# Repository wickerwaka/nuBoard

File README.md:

# nuBoard

The repository includes board hardware, RP2040 firmware, an Efinix runtime
template, and Linux host tools. See [`mcu/README.md`](mcu/README.md),
[`fpga/template/README.md`](fpga/template/README.md),
[`host/README.md`](host/README.md), and [`docs/protocol.md`](docs/protocol.md).

The [68000 differential harness](docs/m68000-harness.md) runs reset-executable
tests against fx68k in Verilator or the FPGA, and supports an explicitly armed
MC68000 daughterboard lane. MCU firmware stays CPU-independent.

KiCad 10 hardware projects copied from the working `nu68020/nuBoard` directory.

| Project | Open this file |
| --- | --- |
| Main board | `hardware/main-board/nuBoard.kicad_pro` |
| Daughter board template | `hardware/daughter-template/nuDaughter.kicad_pro` |
| 68000 daughter board | `hardware/68000/68000.kicad_pro` |
| Motorola 68020 daughter board | `hardware/68020/68020.kicad_pro` |
| Motorola 68020 four-layer alternative | `hardware/68020-4layer/68020-4layer.kicad_pro` |
| Motorola 68030 daughter board | `hardware/68030/68030.kicad_pro` |
| Motorola 68030 four-layer alternative | `hardware/68030-4layer/68030-4layer.kicad_pro` |
| NEC V35S daughter board | `hardware/v35s/v35s.kicad_pro` |

Each daughter project has its own `nuBoard.kicad_sym`, `nuBoard.pretty`, and
project-relative library tables. Either directory can be copied independently;
the only libraries required outside it are the default KiCad 10 libraries.
Keep these local libraries with the project when copying or distributing it.
The main board also uses project-relative custom libraries and bundled models.

To create a daughter board, copy the entire `hardware/daughter-template` directory,
or select it with KiCad's New Project from Template dialog. Its `meta` directory
contains template metadata. Keep the library filenames as `nuBoard.*`; KiCad
renames files containing `nuDaughter` when creating a project from the template.
Filename-specific sheet metadata and annotation history have been removed from
the template settings so new projects can be renamed and annotated cleanly.

Existing production exports, notes, design blocks, models, and supporting data
are preserved beside their projects. Production exports are historical snapshots;
regenerate them before fabrication. Backups and personal editor state were copied
locally but are excluded from Git. The original source directory is untouched.

## Konnect MCP

Open your MCP client from the repository root. `.mcp.json` configures Konnect for
compatible clients; `.codex/config.toml` configures it for Codex, following the
[official MCP configuration documentation](https://developers.openai.com/codex/mcp/).
Codex loads project configuration for trusted projects. Restart the client after
opening this repository to load the server.

Both configurations run `sh scripts/konnect.sh`, which uses `bin/konnect` when
present, otherwise `konnect` on PATH. This checkout includes a local copy of the
existing Konnect v0.2.0 macOS arm64 executable in `bin/konnect`; the binary is
ignored by Git. On another machine, install a compatible Konnect executable on
PATH or place it in `bin/konnect` and make it executable.

Check the installation with `sh scripts/konnect.sh --version` and
`sh scripts/konnect.sh status`. For live PCB operations, open the intended PCB in
KiCad and enable its IPC API. Explicitly select the intended project when using
Konnect because this repository contains three boards.

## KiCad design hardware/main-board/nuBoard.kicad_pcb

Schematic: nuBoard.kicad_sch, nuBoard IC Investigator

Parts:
C1, C131: 4.7u; C_0402_1005Metric; JLCPCB Part C23733
C2, C3, C101, C104, C107, C110, C113, C116, C117, C132, C145, C146, C147, C148, C149, C150, C151, C152, C153, C154, C155, C156, C157, C158, C159, C160, C161, C162, C163, C164, C165, C166, C167, C168, C169, C170, C171, C172, C173, C174, C175, C176, C177, C178, C179, C180, C181, C182, C183, C184, C185, C186, C187, C188, C189, C190, C191, C192, C193, C194: 0.1u; C_0402_1005Metric; JLCPCB Part C1525
C4, C133, C134: 0.01u; C_0402_1005Metric; JLCPCB Part C15195
C5, C6, C7, C8, C9, C10, C11, C12, C13, C14, C15, C16, C17, C18, C19, C20, C21, C22, C23, C24, C25, C26, C27, C28, C29, C30, C31, C32, C33, C34, C35, C36, C37, C38, C39, C118, C119, C120, C121, C122, C123, C124, C125, C128, C129, C130: 0.1u 0201; C_0201_0603Metric; JLCPCB Part C5142565
C40, C41, C42, C43, C44, C45, C46, C47, C48, C49, C50, C51, C52, C53, C54, C55, C56, C57, C58, C59, C60, C61, C62, C63, C64, C65, C66, C67, C68, C69, C70, C71, C72, C73, C74, C75, C76, C77, C78, C79, C80, C81, C82, C83: 0.01u 0201; C_0201_0603Metric; JLCPCB Part C285010
C84, C85, C88, C89: 1u; C_0805_2012Metric; JLCPCB Part C28323
C86, C87, C90, C91, C93, C97, C100, C114, C115: 10u; C_0805_2012Metric; JLCPCB Part C15850
C92, C94, C95, C96, C98, C99, C126, C127: 1u; C_0402_1005Metric; JLCPCB Part C52923
C102, C103, C108, C109: 22u; C_0402_1005Metric; JLCPCB Part C22367823
C105, C106, C111, C112: 10u; C_0402_1005Metric; JLCPCB Part C315248
D1, D2, D3, D4: LED; LED_0603_1608Metric; JLCPCB Part C2286
FB1: 33ohm 100mhz; L_0402_1005Metric; JLCPCB Part C160974
H1, H2, H3, H4, H5, H6: MountingHole_Pad; MountingHole_3.2mm_M3_ISO7380
H7, H8, H9, H10, H11, H12, H13: MountingHole_Pad; MountingHole_3.2mm_M3
J1: FPGA Debug; PinHeader_2x05_P1.27mm_Vertical_SMD; JLCPCB Part C41376037
J2: Barrel_Jack_Switch; BarrelJack_Wuerth_6941xx301002
J3: USB_C_Receptacle_USB2.0_16P; USB_C_Receptacle_HCTL_HC-TYPE-C-16P-01A; JLCPCB Part C2894897
J4: MCU Debug; PinHeader_2x05_P1.27mm_Vertical_SMD; JLCPCB Part C41376037
J5, J6, J7, J8: Conn_01x34_Socket; PinSocket_1x34_P2.54mm_Vertical
L1, L2: 2.2uH; L_1008_2520Metric; JLCPCB Part C964122
Q1: NVF5P03T3G; SOT-223-3_TabPin2; JLCPCB Part C895162
Q2: BSR802NL6327; SOT-23; JLCPCB Part C5240463
R1, R2, R3, R4, R5, R6, R7, R8, R9, R10, R11, R13, R14, R15, R17, R18, R24, R27, R28, R31, R32, R33, R39, R40, R56, R57, R58, R59, R60, R61, R62, R63, R64, R65, R66, R67, R68, R70, R72, R74, R76, R77, R78, R79: 10K; R_0402_1005Metric; JLCPCB Part C25744
R12, R29, R30, R69, R71, R73, R75: 22; R_0402_1005Metric; JLCPCB Part C25092
R16, R19, R35, R38, R42, R43: 1K; R_0402_1005Metric; JLCPCB Part C11702
R20, R21: 5.1K; R_0402_1005Metric; JLCPCB Part C25905
R22: 33.2K 1%; R_0402_1005Metric; JLCPCB Part C122548
R23, R26: 10K 1%; R_0402_1005Metric; JLCPCB Part C25744
R25: 5.76K 1%; R_0402_1005Metric; JLCPCB Part C11590
R34: 400; R_0402_1005Metric; JLCPCB Part C2909358
R36, R37, R41: 27; R_0402_1005Metric; JLCPCB Part C25100
RN1, RN2, RN3, RN4, RN5, RN6, RN7, RN8, RN9, RN10, RN11, RN12, RN13, RN14, RN15, RN16, RN17, RN18, RN19, RN20, RN21, RN22, RN23, RN24: 22R; YC248-JR-0722RL; Manufacturer Part YC248-JR-0722RL; LCSC C695207
SW1: MCU_Reset; SW_SPST_Omron_B3FS-100xP; JLCPCB Part C271750
SW2: MCU_Boot; SW_SPST_Omron_B3FS-100xP; JLCPCB Part C271750
TP1: +5V; TestPoint_Pad_D1.0mm
TP2: +3.3V; TestPoint_Pad_D1.0mm
TP3: +1.2V; TestPoint_Pad_D1.0mm
TP4: VCC_DUT; TestPoint_Pad_D1.0mm
TP5: VCCB; TestPoint_Pad_D1.0mm
U1: T120F484; LFBGA-484_18x18mm_Layout22x22_P0.8mm; JLCPCB Part C3277977
U2: IS66WVH8M8BLL-100B1LI; ISSI_TFBGA-24_6x8mm_P1.0mm; JLCPCB Part C1349096
U3: TPS2116DRL; SOT-583-8; JLCPCB Part C3235557
U4, U5: AP2112K-3.3; SOT-23-5; JLCPCB Part C23380830
U6, U7: TPS563201; SOT-23-6; JLCPCB Part C116592
U8: UCC27524D; SOIC-8_3.9x4.9mm_P1.27mm; JLCPCB Part C465729
U9: TPS2111APWR; SOP65P640X120-8N; JLCPCB Part C471060
U10: W25Q128JVS; SOIC-8_5.3x5.3mm_P1.27mm; JLCPCB Part C97521
U11: RP2040; QFN-56-1EP_7x7mm_P0.4mm_EP3.2x3.2mm; JLCPCB Part C2040
U24, U25, U26, U27, U28, U29, U30, U31, U32, U33, U34, U35: SN74LVC8T245PWR; TSSOP-24_4.4x7.8mm_P0.65mm; JLCPCB Part C27643
U36, U41: TXS0108EPW; TSSOP-20_4.4x6.5mm_P0.65mm; JLCPCB Part C17206
U37, U38, U39, U40: SN74LVC1T45DRL; SOT-563; JLCPCB Part C352970
Y1: 50Mhz; Oscillator_SMD_Abracon_ASE-4Pin_3.2x2.5mm; JLCPCB Part C717684
Y2: 12Mhz; Oscillator_SMD_Abracon_ASE-4Pin_3.2x2.5mm; JLCPCB Part C596950

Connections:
+1.1V_MCU: C127.1, C128.1, C129.1, U11.23 (DVDD), U11.45 (VREG_VOUT), U11.50 (DVDD)
+1.2V: C5.1, C6.1, C7.1, C8.1, C9.1, C10.1, C11.1, C12.1, C13.1, C14.1, C15.1, C16.1, C17.1, C18.1, C19.1, C20.1, C21.1, C40.1, C41.1, C42.1, C43.1, C44.1, C45.1, C46.1, C47.1, C48.1, C49.1, C50.1, C51.1, C52.1, C53.1, C54.1, C55.1, C56.1, C57.1, C58.1, C59.1, C60.1, C61.1, C62.1, C63.1, C64.1, C65.1, C66.1, C67.1, C84.1, C85.1, C86.1, C87.1, C108.1, C109.1, L2.2, R25.1, TP3.1 (1_1), U1.D5 (VCCA_TL), U1.D17 (VCCA_TR), U1.E17 (VCCA_TR), U1.H10 (VCC), U1.J9 (VCC), U1.J11 (VCC), U1.J13 (VCC), U1.J15 (VCC), U1.K10 (VCC), U1.K12 (VCC), U1.K14 (VCC), U1.L9 (VCC), U1.L11 (VCC), U1.L13 (VCC), U1.M8 (VCC), U1.M10 (VCC), U1.M12 (VCC), U1.M14 (VCC), U1.N9 (VCC), U1.N11 (VCC), U1.N13 (VCC), U1.N15 (VCCA_BR), U1.P10 (VCC), U1.P12 (VCC), U1.P14 (VCC), U1.P15 (VCCA_BR), U1.R11 (VCC), U1.W5 (VCCA_BL)
+3.3V: C3.1, C4.1, C22.1, C23.1, C24.1, C25.1, C26.1, C27.1, C28.1, C29.1, C30.1, C31.1, C32.1, C33.1, C34.1, C35.1, C36.1, C37.1, C38.1, C39.1, C68.1, C69.1, C70.1, C71.1, C72.1, C73.1, C74.1, C75.1, C76.1, C77.1, C78.1, C79.1, C80.1, C81.1, C82.1, C83.1, C88.1, C89.1, C90.1, C91.1, C102.1, C103.1, C133.1, C134.1, C145.1, C148.1, C151.1, C154.1, C157.1, C160.1, C163.1, C166.1, C169.1, C172.1, C175.1, C178.1, C181.1, C183.1, C185.1, C187.1, C189.1, C191.1, C192.1, C193.1, FB1.2, J1.1, L1.2, R1.1, R2.1, R3.1, R4.1, R5.1, R6.1, R7.1, R8.1, R9.1, R10.1, R11.1, R13.1, R14.1, R15.1, R22.1, R28.1, R56.1, R57.1, R58.1, R59.1, R60.1, R61.1, R62.1, R63.1, R64.1, R65.1, R66.1, R67.1, R68.1, R77.1, R78.1, R79.1, TP2.1 (1_1), U1.AA4 (VCCIO4F), U1.AA14 (VCCIO4B), U1.B3 (VCCIO2A), U1.B18 (VCCIO3D_TR_BR), U1.C8 (VCCIO2B), U1.C9 (VCCIO2C), U1.C14 (VCCIO2E), U1.C17 (VCCIO2F), U1.C20 (VCCIO3D_TR_BR), U1.D3 (VCCIO2A), U1.D6 (VCCIO2B), U1.D12 (VCCIO2D), U1.F2 (VCCIO1F_1G), U1.F3 (VCCIO1F_1G), U1.F9 (VCCIO2C), U1.F11 (VCCIO2D), U1.F14 (VCCIO2E), U1.G16 (VCCIO2F), U1.J6 (VCCIO1D_1E), U1.K3 (VCCIO1D_1E), U1.N3 (VCCIO1B_1C), U1.N6 (VCCIO1B_1C), U1.R5 (VCCIO1B_1C), U1.R9 (VCCIO4E), U1.T9 (VCCIO4D), U1.T11 (VCCIO4C), U1.U3 (VCCIO1A), U1.U15 (VCCIO4A), U1.V13 (VCCIO4B), U1.W7 (VCCIO4E), U1.Y3 (VCCIO4F), U1.Y9 (VCCIO4D), U1.Y12 (VCCIO4C), U1.Y16 (VCCIO4A), U2.B4 (VCC), U2.D1 (VCCQ), U2.E4 (VCCQ), U24.1 (VCCA), U25.1 (VCCA), U26.1 (VCCA), U27.1 (VCCA), U28.1 (VCCA), U29.1 (VCCA), U30.1 (VCCA), U31.1 (VCCA), U32.1 (VCCA), U33.1 (VCCA), U34.1 (VCCA), U35.1 (VCCA), U36.2 (VCCA), U37.1 (VCCA), U38.1 (VCCA), U39.1 (VCCA), U40.1 (VCCA), U41.2 (VCCA)
+3.3V_DUT: C99.1, C100.1, C116.1, R32.1, R33.1, U5.5 (VOUT), U9.8 (IN1)
+3.3V_MCU: C96.1, C97.1, C118.1, C119.1, C120.1, C121.1, C122.1, C123.1, C124.1, C125.1, C126.1, C130.1, C131.1, C132.1, J4.1, R39.1, R40.1, R42.2, R43.2, U4.5 (VOUT), U10.8 (VCC), U11.1 (IOVDD), U11.10 (IOVDD), U11.22 (IOVDD), U11.33 (IOVDD), U11.42 (IOVDD), U11.43 (ADC_AVDD), U11.44 (VREG_VIN), U11.48 (USB_VDD), U11.49 (IOVDD), Y2.1 (EN), Y2.4 (Vdd)
+5V: C93.1, C95.1, C98.1, C104.1, C105.1, C106.1, C110.1, C111.1, C112.1, C113.1, C114.1, C117.1, TP1.1 (1_1), U3.2 (VOUT), U3.7 (VOUT), U4.1 (VIN), U4.3 (EN), U5.1 (VIN), U5.3 (EN), U6.3 (VIN), U7.3 (VIN), U8.6 (V_{DD}), U9.6 (IN2)
/3V3_SELECT: J6.1, R40.2, U11.32 (GPIO21)
/5V_SELECT: J7.1, R39.2, U11.31 (GPIO20)
/B00: J8.3, RN20.9
/B01: J8.4, RN20.10
/B02: J8.5, RN20.11
/B03: J8.6, RN20.12
/B04: J8.7, RN20.13
/B05: J8.8, RN20.14
/B06: J8.9, RN20.15
/B07: J8.10, RN20.16
/B10: J8.14, RN22.9
/B11: J8.15, RN22.10
/B12: J8.16, RN22.11
/B13: J8.17, RN22.12
/B14: J8.18, RN22.13
/B15: J8.19, RN22.14
/B16: J8.20, RN22.15
/B17: J8.21, RN22.16
/B20: J8.26, RN24.9
/B21: J8.27, RN24.10
/B22: J8.28, RN24.11
/B23: J8.29, RN24.12
/B24: J8.30, RN24.13
/B25: J8.31, RN24.14
/B26: J8.32, RN24.15
/B27: J8.33, RN24.16
/BCLK: J8.12, R75.2
/BX0: J8.22, U36.12 (B8)
/BX1: J8.23, U36.13 (B7)
/BX2: J8.24, U36.14 (B6)
/BX3: J8.25, U36.15 (B5)
/DUT_CROWBAR: R30.1, U1.E1 (GPIOT_TXN01)
/DUT_ISOLATE: R29.1, U1.E5 (GPIOL_162_EXTFB)
/FPGA_1V2_EN: R27.1, U7.5 (EN), U11.36 (GPIO24)
/FPGA_3V3_EN: R24.1, U6.5 (EN), U11.37 (GPIO25)
/FPGA_CBUS0: R5.2, U1.U4 (GPIOL_11_CBUS0), U11.14 (GPIO11)
/FPGA_CBUS1: R6.2, U1.U6 (GPIOL_12_CBUS1), U11.15 (GPIO12)
/FPGA_CBUS2: R7.2, U1.T4 (GPIOL_13_CBUS2), U11.16 (GPIO13)
/FPGA_CCK: U1.W1 (GPIOL_01_CCK), U11.6 (GPIO4)
/FPGA_CDI0: U1.V2 (GPIOL_08_CDI0), U11.2 (GPIO0)
/FPGA_CDI1: U1.V1 (GPIOL_09_CDI1), U11.3 (GPIO1)
/FPGA_CDI2: U1.T6 (GPIOL_14_CDI2), U11.4 (GPIO2)
/FPGA_CDI3: U1.R8 (GPIOL_16_CDI3), U11.5 (GPIO3)
/FPGA_CDONE: R1.2, U1.V5 (CDONE), U11.11 (GPIO8)
/FPGA_CLK_IN: R12.2, U1.A18 (GPIOR_167_PLLIN1), U1.A20 (GPIOR_174_CLK15)
/FPGA_CRESET_N: J1.10, R2.2, U1.V4 (CRESET_N), U11.9 (GPIO7)
/FPGA_CSI: R4.2, U1.V6 (GPIOL_04_CSI), U11.7 (GPIO5)
/FPGA_CSO: U1.U5 (GPIOL_05_CSO), U11.8 (GPIO6)
/FPGA_NSTATUS: U1.F5 (GPIOL_150_NSTATUS), U11.13 (GPIO10)
/FPGA_SS_N: R3.2, U1.V3 (GPIOL_00_SS_N), U11.12 (GPIO9)
/FPGA_TCK: J1.4, R8.2, U1.T1 (TCK), U11.17 (GPIO14)
/FPGA_TDI: J1.8, R9.2, U1.U2 (TDI), U11.18 (GPIO15)
/FPGA_TDO: J1.6, R10.2, U1.T3 (TDO), U11.27 (GPIO16)
/FPGA_TMS: J1.2, R11.2, U1.U1 (TMS), U11.28 (GPIO17)
/F_B00: RN19.8, U1.W2 (GPIOB_TXP04_CDI29)
/F_B0_DIR: U1.Y4 (GPIOB_TXP03_CDI31), U33.2 (DIR)
/F_B01: RN19.7, U1.W3 (GPIOB_TXN04_CDI28)
/F_B1_DIR: U1.V7 (GPIOB_TXP15_CDI15), U34.2 (DIR)
/F_B02: RN19.6, U1.Y1 (GPIOB_TXN05_CDI26)
/F_B2_DIR: U1.W11 (GPIOB_RXP03), U35.2 (DIR)
/F_B03: RN19.5, U1.AA1 (GPIOB_TXP05_CDI27)
/F_B04: RN19.4, U1.AA2 (GPIOB_TXN06_CDI24)
/F_B05: RN19.3, U1.AB2 (GPIOB_TXP06_CDI25)
/F_B06: RN19.2, U1.AB3 (GPIOB_TXP07_CDI23)
/F_B07: RN19.1, U1.W4 (GPIOB_TXN03_CDI30)
/F_B10: RN21.8, U1.AB6 (GPIOB_TXP14_CDI17)
/F_B11: RN21.7, U1.AA6 (GPIOB_TXN14_CDI16)
/F_B12: RN21.6, U1.Y6 (GPIOB_TXP13_CDI19)
/F_B13: RN21.5, U1.AB7 (GPIOB_TXP16_CDI13)
/F_B14: RN21.4, U1.AA7 (GPIOB_TXN16_CDI12)
/F_B15: RN21.3, U1.Y7 (GPIOB_TXN13_CDI18)
/F_B16: RN21.2, U1.AA8 (GPIOB_TXN22)
/F_B17: RN21.1, U1.W8 (GPIOB_TXP17_CDI11)
/F_B20: RN23.8, U1.AB11 (GPIOB_RXP00)
/F_B21: RN23.7, U1.AA11 (GPIOB_RXN00)
/F_B22: RN23.6, U1.R4 (GPIOL_19_PLLIN1)
/F_B23: RN23.5, U1.AB12 (GPIOB_RXN05)
/F_B24: RN23.4, U1.AA12 (GPIOB_RXP05)
/F_B25: RN23.3, U1.W12 (GPIOB_RXN08_EXTFB0)
/F_B26: RN23.2, U1.V12 (GPIOB_RXP08_EXTFB0)
/F_B27: RN23.1, U1.AA13 (GPIOB_RXN10)
/F_BCLK: U1.AA5 (GPIOB_TXP08_CDI21), U40.3 (A)
/F_BCLK_EN: R76.1, U1.AB5 (GPIOB_TXN08_CDI20), U40.5 (DIR)
/F_BX0: U1.AB8 (GPIOB_TXP22), U36.9 (A8)
/F_BX1: U1.AA9 (GPIOB_TXN24), U36.8 (A7)
/F_BX2: U1.W9 (GPIOB_TXN19), U36.7 (A6)
/F_BX3: U1.AB10 (GPIOB_TXP26), U36.6 (A5)
/F_L00: RN1.8, U1.A3 (GPIOT_TXN06)
/F_L0_DIR: U1.E3 (GPIOL_160_PLLIN1), U24.2 (DIR)
/F_L01: RN1.7, U1.A2 (GPIOT_TXP05)
/F_L1_DIR: U1.L5 (GPIOL_71_CLK5), U25.2 (DIR)
/F_L02: RN1.6, U1.B2 (GPIOT_TXN05)
/F_L2_DIR: U1.R2 (GPIOL_15_PLLIN0), U26.2 (DIR)
/F_L03: RN1.5, U1.B1 (GPIOT_TXN04)
/F_L04: RN1.4, U1.C2 (GPIOT_TXN02)
/F_L05: RN1.3, U1.C1 (GPIOT_TXP04)
/F_L06: RN1.2, U1.D2 (GPIOT_TXP02)
/F_L07: RN1.1, U1.D1 (GPIOT_TXP01)
/F_L10: RN3.8, U1.H6 (GPIOL_123)
/F_L11: RN3.7, U1.H4 (GPIOL_121)
/F_L12: RN3.6, U1.J7 (GPIOL_115)
/F_L13: RN3.5, U1.J5 (GPIOL_85)
/F_L14: RN3.4, U1.J4 (GPIOL_88)
/F_L15: RN3.3, U1.K5 (GPIOL_81)
/F_L16: RN3.2, U1.K4 (GPIOL_79)
/F_L17: RN3.1, U1.L6 (GPIOL_72_CLK6)
/F_L20: RN5.8, U1.N4 (GPIOL_56)
/F_L21: RN5.7, U1.M4 (GPIOL_64_CTRL2)
/F_L22: RN5.6, U1.N1 (GPIOL_62_CTRL0)
/F_L23: RN5.5, U1.N2 (GPIOL_63_CTRL1)
/F_L24: RN5.4, U1.P1 (GPIOL_52)
/F_L25: RN5.3, U1.P2 (GPIOL_50)
/F_L26: RN5.2, U1.P3 (GPIOL_51)
/F_L27: RN5.1, U1.R1 (GPIOL_49)
/F_LCLK: U1.G5 (GPIOL_147), U37.3 (A)
/F_LCLK_EN: R70.1, U1.G4 (GPIOL_138), U37.5 (DIR)
/F_LX0: U1.D9 (GPIOT_TXN21), U41.6 (A5)
/F_LX1: U1.E10 (GPIOT_TXN24), U41.7 (A6)
/F_LX2: U1.E12 (GPIOT_RXN09_CLKN0), U41.8 (A7)
/F_LX3: U1.F10 (GPIOT_TXP26), U41.9 (A8)
/F_R00: RN13.8, U1.AB13 (GPIOB_RXP10)
/F_R0_DIR: U1.V15 (GPIOB_RXP29_CLKP2), U30.2 (DIR)
/F_R01: RN13.7, U1.AB14 (GPIOB_RXN14)
/F_R1_DIR: U1.B19 (GPIOR_172_CTRL13), U31.2 (DIR)
/F_R02: RN13.6, U1.AB15 (GPIOB_RXP14)
/F_R2_DIR: U1.B17 (GPIOT_RXN21), U32.2 (DIR)
/F_R03: RN13.5, U1.Y14 (GPIOB_RXP16)
/F_R04: RN13.4, U1.W14 (GPIOB_RXN19_CLKN1)
/F_R05: RN13.3, U1.V14 (GPIOB_RXP19_CLKP1)
/F_R06: RN13.2, U1.U14 (GPIOB_RXN18_EXTFB1)
/F_R07: RN13.1, U1.AA15 (GPIOB_RXN20)
/F_R10: RN15.8, U1.D22 (GPIOR_183_CTRL10)
/F_R11: RN15.7, U1.D19 (GPIOR_173_CTRL12)
/F_R12: RN15.6, U1.C22 (GPIOR_182_CTRL11)
/F_R13: RN15.5, U1.C21 (GPIOR_178_CTRL11)
/F_R14: RN15.4, U1.C19 (GPIOR_171_CTRL14)
/F_R15: RN15.3, U1.B22 (GPIOR_180_CLK9)
/F_R16: RN15.2, U1.B21 (GPIOR_177_CLK12)
/F_R17: RN15.1, U1.B20 (GPIOR_175_CLK14)
/F_R20: RN17.8, U1.D18 (GPIOR_168_PLLIN2)
/F_R21: RN17.7, U1.C18 (GPIOR_166_PLLIN0)
/F_R22: RN17.6, U1.A19 (GPIOR_169_MREFCLK)
/F_R23: RN17.5, U1.D15 (GPIOT_RXN22)
/F_R24: RN17.4, U1.C16 (GPIOT_RXP23)
/F_R25: RN17.3, U1.C15 (GPIOT_RXN23)
/F_R26: RN17.2, U1.B16 (GPIOT_RXN20)
/F_R27: RN17.1, U1.A17 (GPIOT_RXP21)
/F_RCLK: U1.D20 (GPIOR_179_CLK10), U38.3 (A)
/F_RCLK_EN: R72.1, U1.D21 (GPIOR_184_CTRL9), U38.5 (DIR)
/F_RX0: U1.V11 (GPIOB_RXN03), U36.1 (A1)
/F_RX1: U1.V10 (GPIOB_TXN25), U36.3 (A2)
/F_RX2: U1.W10 (GPIOB_TXP25), U36.4 (A3)
/F_RX3: U1.AA10 (GPIOB_TXN26), U36.5 (A4)
/F_T00: RN7.8, U1.B15 (GPIOT_RXP18_EXTFB1)
/F_T0_DIR: U1.A12 (GPIOT_RXP11), U27.2 (DIR)
/F_T01: RN7.7, U1.A15 (GPIOT_RXN18_EXTFB1)
/F_T1_DIR: U1.A8 (GPIOT_TXN18), U28.2 (DIR)
/F_T02: RN7.6, U1.D14 (GPIOT_RXN19_CLKN1)
/F_T2_DIR: U1.A4 (GPIOT_TXP06), U29.2 (DIR)
/F_T03: RN7.5, U1.B14 (GPIOT_RXP15)
/F_T04: RN7.4, U1.A14 (GPIOT_RXN15)
/F_T05: RN7.3, U1.C13 (GPIOT_RXN13)
/F_T06: RN7.2, U1.B13 (GPIOT_RXP13)
/F_T07: RN7.1, U1.A13 (GPIOT_RXN11)
/F_T10: RN9.8, U1.B11 (GPIOT_RXN01)
/F_T11: RN9.7, U1.A11 (GPIOT_RXP01)
/F_T12: RN9.6, U1.D10 (GPIOT_TXP24)
/F_T13: RN9.5, U1.B10 (GPIOT_TXN25)
/F_T14: RN9.4, U1.A10 (GPIOT_TXP25)
/F_T15: RN9.3, U1.B9 (GPIOT_TXN23)
/F_T16: RN9.2, U1.A9 (GPIOT_TXP23)
/F_T17: RN9.1, U1.B8 (GPIOT_TXP18)
/F_T20: RN11.8, U1.A7 (GPIOT_TXP14)
/F_T21: RN11.7, U1.B7 (GPIOT_TXN14)
/F_T22: RN11.6, U1.A6 (GPIOT_TXP12)
/F_T23: RN11.5, U1.B6 (GPIOT_TXN12)
/F_T24: RN11.4, U1.C6 (GPIOT_TXP10)
/F_T25: RN11.3, U1.A5 (GPIOT_TXP07)
/F_T26: RN11.2, U1.B5 (GPIOT_TXN07)
/F_T27: RN11.1, U1.C4 (GPIOT_TXN03)
/F_TCLK: U1.D11 (GPIOT_RXN02), U39.3 (A)
/F_TCLK_EN: R74.1, U1.C11 (GPIOT_RXP04), U39.5 (DIR)
/F_TX0: U1.E6 (GPIOT_TXN11), U41.1 (A1)
/F_TX1: U1.F6 (GPIOT_TXP11), U41.3 (A2)
/F_TX2: U1.P5 (GPIOL_47), U41.4 (A3)
/F_TX3: U1.E8 (GPIOT_TXP16), U41.5 (A4)
/HR_CK: U1.M1 (GPIOL_65_CTRL3), U2.B2 (CK)
/HR_CS_N: R77.2, U1.G3 (GPIOL_141), U2.A3 (~CS)
/HR_DQ0: U1.K1 (GPIOL_87), U2.D3 (DQ0)
/HR_DQ1: U1.L1 (GPIOL_68_CLK2), U2.D2 (DQ1)
/HR_DQ2: U1.H1 (GPIOL_133), U2.C4 (DQ2)
/HR_DQ3: U1.J1 (GPIOL_119), U2.D4 (DQ3)
/HR_DQ4: U1.G1 (GPIOL_136), U2.D5 (DQ4)
/HR_DQ5: U1.K2 (GPIOL_89), U2.E3 (DQ5)
/HR_DQ6: U1.L2 (GPIOL_69_CLK3), U2.E2 (DQ6)
/HR_DQ7: U1.M3 (GPIOL_67_CLK1), U2.E1 (DQ7)
/HR_RESET_N: R78.2, U1.G2 (GPIOL_142), U2.A4 (~RESET)
/HR_RWDS: U1.L3 (GPIOL_73_CLK7), U2.C3 (RWDS)
/L00: J5.3, RN2.9
/L01: J5.4, RN2.10
/L02: J5.5, RN2.11
/L03: J5.6, RN2.12
/L04: J5.7, RN2.13
/L05: J5.8, RN2.14
/L06: J5.9, RN2.15
/L07: J5.10, RN2.16
/L10: J5.14, RN4.9
/L11: J5.15, RN4.10
/L12: J5.16, RN4.11
/L13: J5.17, RN4.12
/L14: J5.18, RN4.13
/L15: J5.19, RN4.14
/L16: J5.20, RN4.15
/L17: J5.21, RN4.16
/L20: J5.26, RN6.9
/L21: J5.27, RN6.10
/L22: J5.28, RN6.11
/L23: J5.29, RN6.12
/L24: J5.30, RN6.13
/L25: J5.31, RN6.14
/L26: J5.32, RN6.15
/L27: J5.33, RN6.16
/LCLK: J5.12, R69.2
/LX0: J5.22, U41.15 (B5)
/LX1: J5.23, U41.14 (B6)
/LX2: J5.24, U41.13 (B7)
/LX3: J5.25, U41.12 (B8)
/MCU_LED1: D3.1 (K), U11.41 (GPIO29/ADC3)
/MCU_LED2: D4.1 (K), U11.40 (GPIO28/ADC2)
/MCU_QSPI_SCLK: U10.6 (CLK), U11.52 (QSPI_SCLK)
/MCU_QSPI_SD0: U10.5 (DI/IO_{0}), U11.53 (QSPI_SD0)
/MCU_QSPI_SD1: U10.2 (DO/IO_{1}), U11.55 (QSPI_SD1)
/MCU_QSPI_SD2: U10.3 (~WP/IO_{2}), U11.54 (QSPI_SD2)
/MCU_QSPI_SD3: U10.7 (~HOLD/~RESET/IO_{3}), U11.51 (QSPI_SD3)
/MCU_RESET_N: J4.10, R35.2, U11.26 (RUN)
/MCU_SWCLK: J4.4, U11.24 (SWCLK)
/MCU_SWDIO: J4.2, U11.25 (SWDIO)
/R00: J7.3, RN14.9
/R01: J7.4, RN14.10
/R02: J7.5, RN14.11
/R03: J7.6, RN14.12
/R04: J7.7, RN14.13
/R05: J7.8, RN14.14
/R06: J7.9, RN14.15
/R07: J7.10, RN14.16
/R10: J7.14, RN16.9
/R11: J7.15, RN16.10
/R12: J7.16, RN16.11
/R13: J7.17, RN16.12
/R14: J7.18, RN16.13
/R15: J7.19, RN16.14
/R16: J7.20, RN16.15
/R17: J7.21, RN16.16
/R20: J7.26, RN18.9
/R21: J7.27, RN18.10
/R22: J7.28, RN18.11
/R23: J7.29, RN18.12
/R24: J7.30, RN18.13
/R25: J7.31, RN18.14
/R26: J7.32, RN18.15
/R27: J7.33, RN18.16
/RCLK: J7.12, R71.2
/RX0: J7.22, U36.20 (B1)
/RX1: J7.23, U36.18 (B2)
/RX2: J7.24, U36.17 (B3)
/RX3: J7.25, U36.16 (B4)
/T00: J6.3, RN8.9
/T01: J6.4, RN8.10
/T02: J6.5, RN8.11
/T03: J6.6, RN8.12
/T04: J6.7, RN8.13
/T05: J6.8, RN8.14
/T06: J6.9, RN8.15
/T07: J6.10, RN8.16
/T10: J6.14, RN10.9
/T11: J6.15, RN10.10
/T12: J6.16, RN10.11
/T13: J6.17, RN10.12
/T14: J6.18, RN10.13
/T15: J6.19, RN10.14
/T16: J6.20, RN10.15
/T17: J6.21, RN10.16
/T20: J6.26, RN12.9
/T21: J6.27, RN12.10
/T22: J6.28, RN12.11
/T23: J6.29, RN12.12
/T24: J6.30, RN12.13
/T25: J6.31, RN12.14
/T26: J6.32, RN12.15
/T27: J6.33, RN12.16
/TCLK: J6.12, R73.2
/TX0: J6.22, U41.20 (B1)
/TX1: J6.23, U41.18 (B2)
/TX2: J6.24, U41.17 (B3)
/TX3: J6.25, U41.16 (B4)
/USB_DN: J3.A7 (D-), J3.B7 (D-), R36.1
/USB_DP: J3.A6 (D+), J3.B6 (D+), R37.1
/VCCB_MUX_D0: R33.2, U9.1 (D0), U11.30 (GPIO19)
/VCCB_MUX_D1: R32.2, U9.2 (D1), U11.29 (GPIO18)
/~F_B0_OE: R65.2, U1.AB4 (GPIOB_TXN07_CDI22), U33.22 (~OE)
/~F_B1_OE: R66.2, U1.V8 (GPIOB_TXN17_CDI10), U34.22 (~OE)
/~F_B2_OE: R67.2, U1.Y13 (GPIOB_RXN16), U35.22 (~OE)
/~F_L0_OE: R56.2, U1.E4 (GPIOL_164_PLLIN0), U24.22 (~OE)
/~F_L1_OE: R57.2, U1.L4 (GPIOL_74_CTRL4), U25.22 (~OE)
/~F_L2_OE: R58.2, U1.R3 (GPIOL_17_EXTFB0), U26.22 (~OE)
/~F_R0_OE: R62.2, U1.W15 (GPIOB_RXN29_CLKN2), U30.22 (~OE)
/~F_R1_OE: R63.2, U1.A21 (GPIOR_176_CLK13), U31.22 (~OE)
/~F_R2_OE: R64.2, U1.A16 (GPIOT_RXP20), U32.22 (~OE)
/~F_T0_OE: R59.2, U1.C12 (GPIOT_RXN04), U27.22 (~OE)
/~F_T1_OE: R60.2, U1.C7 (GPIOT_TXN10), U28.22 (~OE)
/~F_T2_OE: R61.2, U1.C3 (GPIOT_TXP03), U29.22 (~OE)
/~F_X_OE: R68.2, R79.2, U1.AB9 (GPIOB_TXP24), U36.10 (OE), U41.10 (OE)
/~MCU_QSPI_SS: R38.2, U10.1 (~CS), U11.56 (~QSPI_SS)
GND: C1.2, C2.2, C3.2, C4.2, C5.2, C6.2, C7.2, C8.2, C9.2, C10.2, C11.2, C12.2, C13.2, C14.2, C15.2, C16.2, C17.2, C18.2, C19.2, C20.2, C21.2, C22.2, C23.2, C24.2, C25.2, C26.2, C27.2, C28.2, C29.2, C30.2, C31.2, C32.2, C33.2, C34.2, C35.2, C36.2, C37.2, C38.2, C39.2, C40.2, C41.2, C42.2, C43.2, C44.2, C45.2, C46.2, C47.2, C48.2, C49.2, C50.2, C51.2, C52.2, C53.2, C54.2, C55.2, C56.2, C57.2, C58.2, C59.2, C60.2, C61.2, C62.2, C63.2, C64.2, C65.2, C66.2, C67.2, C68.2, C69.2, C70.2, C71.2, C72.2, C73.2, C74.2, C75.2, C76.2, C77.2, C78.2, C79.2, C80.2, C81.2, C82.2, C83.2, C84.2, C85.2, C86.2, C87.2, C88.2, C89.2, C90.2, C91.2, C92.2, C93.2, C94.2, C95.2, C96.2, C97.2, C98.2, C99.2, C100.2, C102.2, C103.2, C104.2, C105.2, C106.2, C108.2, C109.2, C110.2, C111.2, C112.2, C113.2, C114.2, C115.2, C116.2, C117.2, C118.2, C119.2, C120.2, C121.2, C122.2, C123.2, C124.2, C125.2, C126.2, C127.2, C128.2, C129.2, C130.2, C131.2, C132.2, C133.2, C134.2, C145.2, C146.2, C147.2, C148.2, C149.2, C150.2, C151.2, C152.2, C153.2, C154.2, C155.2, C156.2, C157.2, C158.2, C159.2, C160.2, C161.2, C162.2, C163.2, C164.2, C165.2, C166.2, C167.2, C168.2, C169.2, C170.2, C171.2, C172.2, C173.2, C174.2, C175.2, C176.2, C177.2, C178.2, C179.2, C180.2, C181.2, C182.2, C183.2, C184.2, C185.2, C186.2, C187.2, C188.2, C189.2, C190.2, C191.2, C192.2, C193.2, C194.2, D1.1 (K), D2.1 (K), J1.3, J1.5, J1.9, J2.2, J3.A1 (GND), J3.A12 (GND), J3.B1 (GND), J3.B12 (GND), J3.SH (SHIELD), J4.3, J4.5, J4.9, J5.1, J5.2, J5.11, J5.13, J6.2, J6.11, J6.13, J7.2, J7.11, J7.13, J8.1, J8.2, J8.11, J8.13, Q2.2 (S), R18.2, R20.2, R21.2, R23.2, R24.2, R26.2, R27.2, R31.2, R34.2, R70.2, R72.2, R74.2, R76.2, SW1.2, SW2.2, U1.A1 (GND), U1.A22 (GND), U1.AB1 (GND), U1.AB22 (GND), U1.B4 (GND), U1.B12 (GND), U1.D4 (GND), U1.D7 (GND), U1.D13 (GND), U1.D16 (GND), U1.E18 (GND), U1.E20 (GND), U1.F22 (GND), U1.H2 (GND), U1.H5 (GND), U1.H15 (GND), U1.H17 (GND), U1.H22 (GND), U1.J10 (GND), U1.J12 (GND), U1.J14 (GND), U1.J20 (GND), U1.K9 (GND), U1.K11 (GND), U1.K13 (GND), U1.K16 (GND), U1.K17 (DDR_VREF), U1.K18 (GND), U1.L8 (GND), U1.L10 (GND), U1.L12 (GND), U1.L14 (GND), U1.M2 (GND), U1.M5 (GND), U1.M9 (GND), U1.M11 (GND), U1.M13 (GND), U1.N8 (GND), U1.N10 (GND), U1.N12 (GND), U1.N14 (GND), U1.N16 (GND), U1.N18 (GND), U1.N20 (GND), U1.N22 (GND), U1.P9 (GND), U1.P11 (GND), U1.P13 (GND), U1.T2 (GND), U1.T5 (GND), U1.T7 (GND), U1.T16 (GND), U1.T18 (GND), U1.U20 (GND), U1.U22 (GND), U1.W13 (GND), U1.W18 (GND), U1.Y2 (GND), U1.Y5 (GND), U1.Y8 (GND), U1.Y11 (GND), U1.Y15 (GND), U1.Y20 (GND), U2.B3 (VSS), U2.C1 (VSSQ), U2.E5 (VSSQ), U3.1 (GND), U4.2 (GND), U5.2 (GND), U6.1 (GND), U7.1 (GND), U8.3 (GND), U9.5 (GND), U10.4 (GND), U11.19 (TESTEN), U11.57 (GND), U24.11 (GND), U24.12 (GND), U24.13 (GND), U25.11 (GND), U25.12 (GND), U25.13 (GND), U26.11 (GND), U26.12 (GND), U26.13 (GND), U27.11 (GND), U27.12 (GND), U27.13 (GND), U28.11 (GND), U28.12 (GND), U28.13 (GND), U29.11 (GND), U29.12 (GND), U29.13 (GND), U30.11 (GND), U30.12 (GND), U30.13 (GND), U31.11 (GND), U31.12 (GND), U31.13 (GND), U32.11 (GND), U32.12 (GND), U32.13 (GND), U33.11 (GND), U33.12 (GND), U33.13 (GND), U34.11 (GND), U34.12 (GND), U34.13 (GND), U35.11 (GND), U35.12 (GND), U35.13 (GND), U36.11 (GND), U37.2 (GND), U38.2 (GND), U39.2 (GND), U40.2 (GND), U41.11 (GND), Y1.2 (GND), Y2.2 (GND)
unnamed: D1.2 (A), R16.1
unnamed: D2.2 (A), R19.1
unnamed: D3.2 (A), R42.1
unnamed: D4.2 (A), R43.1
unnamed: J3.A5 (CC1), R21.1
unnamed: J3.B5 (CC2), R20.1
unnamed: Q1.1 (G), U8.7 (OUTA)
unnamed: Q2.1 (G), U8.5 (OUTB)
unnamed: R35.1, SW1.1
unnamed: R38.1, SW2.1
unnamed: R13.2, U1.F1 (GPIOL_151_TEST_N)
unnamed: R14.2, U1.F4 (GPIOL_156_CBSEL0)
unnamed: R15.2, U1.E2 (GPIOL_157_CBSEL1)
unnamed: C92.1, J2.1, R16.2, R17.1, U3.3 (VIN1), U3.5 (MODE)
unnamed: R17.2, R18.1, U3.4 (PR1)
unnamed: C94.1, J3.A4 (VBUS), J3.A9 (VBUS), J3.B4 (VBUS), J3.B9 (VBUS), R19.2, U3.6 (VIN2)
unnamed: C101.1, L1.1, U6.2 (SW)
unnamed: C101.2, U6.6 (VBST)
unnamed: R22.2, R23.1, U6.4 (VFB)
unnamed: C107.1, L2.1, U7.2 (SW)
unnamed: C107.2, U7.6 (VBST)
unnamed: R25.2, R26.1, U7.4 (VFB)
unnamed: R28.2, R29.2, U8.2 (INA)
unnamed: R30.2, R31.1, U8.4 (INB)
unnamed: R34.1, U9.4 (ILIM)
unnamed: R36.2, U11.46 (USB_DM)
unnamed: R37.2, U11.47 (USB_DP)
unnamed: R41.2, U11.20 (XIN)
unnamed: RN1.16, U24.3 (A1)
unnamed: RN1.15, U24.4 (A2)
unnamed: RN1.14, U24.5 (A3)
unnamed: RN1.13, U24.6 (A4)
unnamed: RN1.12, U24.7 (A5)
unnamed: RN1.11, U24.8 (A6)
unnamed: RN1.10, U24.9 (A7)
unnamed: RN1.9, U24.10 (A8)
unnamed: RN2.1, U24.21 (B1)
unnamed: RN2.2, U24.20 (B2)
unnamed: RN2.3, U24.19 (B3)
unnamed: RN2.4, U24.18 (B4)
unnamed: RN2.5, U24.17 (B5)
unnamed: RN2.6, U24.16 (B6)
unnamed: RN2.7, U24.15 (B7)
unnamed: RN2.8, U24.14 (B8)
unnamed: RN3.16, U25.3 (A1)
unnamed: RN3.15, U25.4 (A2)
unnamed: RN3.14, U25.5 (A3)
unnamed: RN3.13, U25.6 (A4)
unnamed: RN3.12, U25.7 (A5)
unnamed: RN3.11, U25.8 (A6)
unnamed: RN3.10, U25.9 (A7)
unnamed: RN3.9, U25.10 (A8)
unnamed: RN4.1, U25.21 (B1)
unnamed: RN4.2, U25.20 (B2)
unnamed: RN4.3, U25.19 (B3)
unnamed: RN4.4, U25.18 (B4)
unnamed: RN4.5, U25.17 (B5)
unnamed: RN4.6, U25.16 (B6)
unnamed: RN4.7, U25.15 (B7)
unnamed: RN4.8, U25.14 (B8)
unnamed: RN5.16, U26.3 (A1)
unnamed: RN5.15, U26.4 (A2)
unnamed: RN5.14, U26.5 (A3)
unnamed: RN5.13, U26.6 (A4)
unnamed: RN5.12, U26.7 (A5)
unnamed: RN5.11, U26.8 (A6)
unnamed: RN5.10, U26.9 (A7)
unnamed: RN5.9, U26.10 (A8)
unnamed: RN6.1, U26.21 (B1)
unnamed: RN6.2, U26.20 (B2)
unnamed: RN6.3, U26.19 (B3)
unnamed: RN6.4, U26.18 (B4)
unnamed: RN6.5, U26.17 (B5)
unnamed: RN6.6, U26.16 (B6)
unnamed: RN6.7, U26.15 (B7)
unnamed: RN6.8, U26.14 (B8)
unnamed: RN7.16, U27.3 (A1)
unnamed: RN7.15, U27.4 (A2)
unnamed: RN7.14, U27.5 (A3)
unnamed: RN7.13, U27.6 (A4)
unnamed: RN7.12, U27.7 (A5)
unnamed: RN7.11, U27.8 (A6)
unnamed: RN7.10, U27.9 (A7)
unnamed: RN7.9, U27.10 (A8)
unnamed: RN8.1, U27.21 (B1)
unnamed: RN8.2, U27.20 (B2)
unnamed: RN8.3, U27.19 (B3)
unnamed: RN8.4, U27.18 (B4)
unnamed: RN8.5, U27.17 (B5)
unnamed: RN8.6, U27.16 (B6)
unnamed: RN8.7, U27.15 (B7)
unnamed: RN8.8, U27.14 (B8)
unnamed: RN9.16, U28.3 (A1)
unnamed: RN9.15, U28.4 (A2)
unnamed: RN9.14, U28.5 (A3)
unnamed: RN9.13, U28.6 (A4)
unnamed: RN9.12, U28.7 (A5)
unnamed: RN9.11, U28.8 (A6)
unnamed: RN9.10, U28.9 (A7)
unnamed: RN9.9, U28.10 (A8)
unnamed: RN10.1, U28.21 (B1)
unnamed: RN10.2, U28.20 (B2)
unnamed: RN10.3, U28.19 (B3)
unnamed: RN10.4, U28.18 (B4)
unnamed: RN10.5, U28.17 (B5)
unnamed: RN10.6, U28.16 (B6)
unnamed: RN10.7, U28.15 (B7)
unnamed: RN10.8, U28.14 (B8)
unnamed: RN11.16, U29.3 (A1)
unnamed: RN11.15, U29.4 (A2)
unnamed: RN11.14, U29.5 (A3)
unnamed: RN11.13, U29.6 (A4)
unnamed: RN11.12, U29.7 (A5)
unnamed: RN11.11, U29.8 (A6)
unnamed: RN11.10, U29.9 (A7)
unnamed: RN11.9, U29.10 (A8)
unnamed: RN12.1, U29.21 (B1)
unnamed: RN12.2, U29.20 (B2)
unnamed: RN12.3, U29.19 (B3)
unnamed: RN12.4, U29.18 (B4)
unnamed: RN12.5, U29.17 (B5)
unnamed: RN12.6, U29.16 (B6)
unnamed: RN12.7, U29.15 (B7)
unnamed: RN12.8, U29.14 (B8)
unnamed: RN13.16, U30.3 (A1)
unnamed: RN13.15, U30.4 (A2)
unnamed: RN13.14, U30.5 (A3)
unnamed: RN13.13, U30.6 (A4)
unnamed: RN13.12, U30.7 (A5)
unnamed: RN13.11, U30.8 (A6)
unnamed: RN13.10, U30.9 (A7)
unnamed: RN13.9, U30.10 (A8)
unnamed: RN14.1, U30.21 (B1)
unnamed: RN14.2, U30.20 (B2)
unnamed: RN14.3, U30.19 (B3)
unnamed: RN14.4, U30.18 (B4)
unnamed: RN14.5, U30.17 (B5)
unnamed: RN14.6, U30.16 (B6)
unnamed: RN14.7, U30.15 (B7)
unnamed: RN14.8, U30.14 (B8)
unnamed: RN15.16, U31.3 (A1)
unnamed: RN15.15, U31.4 (A2)
unnamed: RN15.14, U31.5 (A3)
unnamed: RN15.13, U31.6 (A4)
unnamed: RN15.12, U31.7 (A5)
unnamed: RN15.11, U31.8 (A6)
unnamed: RN15.10, U31.9 (A7)
unnamed: RN15.9, U31.10 (A8)
unnamed: RN16.1, U31.21 (B1)
unnamed: RN16.2, U31.20 (B2)
unnamed: RN16.3, U31.19 (B3)
unnamed: RN16.4, U31.18 (B4)
unnamed: RN16.5, U31.17 (B5)
unnamed: RN16.6, U31.16 (B6)
unnamed: RN16.7, U31.15 (B7)
unnamed: RN16.8, U31.14 (B8)
unnamed: RN17.16, U32.3 (A1)
unnamed: RN17.15, U32.4 (A2)
unnamed: RN17.14, U32.5 (A3)
unnamed: RN17.13, U32.6 (A4)
unnamed: RN17.12, U32.7 (A5)
unnamed: RN17.11, U32.8 (A6)
unnamed: RN17.10, U32.9 (A7)
unnamed: RN17.9, U32.10 (A8)
unnamed: RN18.1, U32.21 (B1)
unnamed: RN18.2, U32.20 (B2)
unnamed: RN18.3, U32.19 (B3)
unnamed: RN18.4, U32.18 (B4)
unnamed: RN18.5, U32.17 (B5)
unnamed: RN18.6, U32.16 (B6)
unnamed: RN18.7, U32.15 (B7)
unnamed: RN18.8, U32.14 (B8)
unnamed: RN19.16, U33.3 (A1)
unnamed: RN19.15, U33.4 (A2)
unnamed: RN19.14, U33.5 (A3)
unnamed: RN19.13, U33.6 (A4)
unnamed: RN19.12, U33.7 (A5)
unnamed: RN19.11, U33.8 (A6)
unnamed: RN19.10, U33.9 (A7)
unnamed: RN19.9, U33.10 (A8)
unnamed: RN20.1, U33.21 (B1)
unnamed: RN20.2, U33.20 (B2)
unnamed: RN20.3, U33.19 (B3)
unnamed: RN20.4, U33.18 (B4)
unnamed: RN20.5, U33.17 (B5)
unnamed: RN20.6, U33.16 (B6)
unnamed: RN20.7, U33.15 (B7)
unnamed: RN20.8, U33.14 (B8)
unnamed: RN21.16, U34.3 (A1)
unnamed: RN21.15, U34.4 (A2)
unnamed: RN21.14, U34.5 (A3)
unnamed: RN21.13, U34.6 (A4)
unnamed: RN21.12, U34.7 (A5)
unnamed: RN21.11, U34.8 (A6)
unnamed: RN21.10, U34.9 (A7)
unnamed: RN21.9, U34.10 (A8)
unnamed: RN22.1, U34.21 (B1)
unnamed: RN22.2, U34.20 (B2)
unnamed: RN22.3, U34.19 (B3)
unnamed: RN22.4, U34.18 (B4)
unnamed: RN22.5, U34.17 (B5)
unnamed: RN22.6, U34.16 (B6)
unnamed: RN22.7, U34.15 (B7)
unnamed: RN22.8, U34.14 (B8)
unnamed: RN23.16, U35.3 (A1)
unnamed: RN23.15, U35.4 (A2)
unnamed: RN23.14, U35.5 (A3)
unnamed: RN23.13, U35.6 (A4)
unnamed: RN23.12, U35.7 (A5)
unnamed: RN23.11, U35.8 (A6)
unnamed: RN23.10, U35.9 (A7)
unnamed: RN23.9, U35.10 (A8)
unnamed: RN24.1, U35.21 (B1)
unnamed: RN24.2, U35.20 (B2)
unnamed: RN24.3, U35.19 (B3)
unnamed: RN24.4, U35.18 (B4)
unnamed: RN24.5, U35.17 (B5)
unnamed: RN24.6, U35.16 (B6)
unnamed: RN24.7, U35.15 (B7)
unnamed: RN24.8, U35.14 (B8)
unnamed: R69.1, U37.4 (B)
unnamed: R71.1, U38.4 (B)
unnamed: R73.1, U39.4 (B)
unnamed: R75.1, U40.4 (B)
unnamed: C1.1, C2.1, FB1.1, Y1.1 (EN), Y1.4 (Vdd)
unnamed: R12.1, Y1.3 (OUT)
unnamed: R41.1, Y2.3 (OUT)
VCCB: C115.1, C146.1, C147.1, C149.1, C150.1, C152.1, C153.1, C155.1, C156.1, C158.1, C159.1, C161.1, C162.1, C164.1, C165.1, C167.1, C168.1, C170.1, C171.1, C173.1, C174.1, C176.1, C177.1, C179.1, C180.1, C182.1, C184.1, C186.1, C188.1, C190.1, C194.1, Q1.3 (S), TP5.1 (1_1), U9.7 (OUT), U24.23 (VCCB), U24.24 (VCCB), U25.23 (VCCB), U25.24 (VCCB), U26.23 (VCCB), U26.24 (VCCB), U27.23 (VCCB), U27.24 (VCCB), U28.23 (VCCB), U28.24 (VCCB), U29.23 (VCCB), U29.24 (VCCB), U30.23 (VCCB), U30.24 (VCCB), U31.23 (VCCB), U31.24 (VCCB), U32.23 (VCCB), U32.24 (VCCB), U33.23 (VCCB), U33.24 (VCCB), U34.23 (VCCB), U34.24 (VCCB), U35.23 (VCCB), U35.24 (VCCB), U36.19 (VCCB), U37.6 (VCCB), U38.6 (VCCB), U39.6 (VCCB), U40.6 (VCCB), U41.19 (VCCB)
VCC_DUT: J5.34, J6.34, J7.34, J8.34, Q1.2 (D), Q2.3 (D), TP4.1 (1_1)

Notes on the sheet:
C5 close to pin 44
Replace with TPS2111A?
RP2350 Microcontroller
HyperRAM: F.Cu-only, no vias; CK/DQ[7:0]/RWDS verified PCB length spread 0.214807mm (limit 0.381mm). U2 and signal tracks locked. Package skew excluded;
Extraction Holes
Mounting Holes
USB and Power Input
C6 close to pin 45
Power Regulation

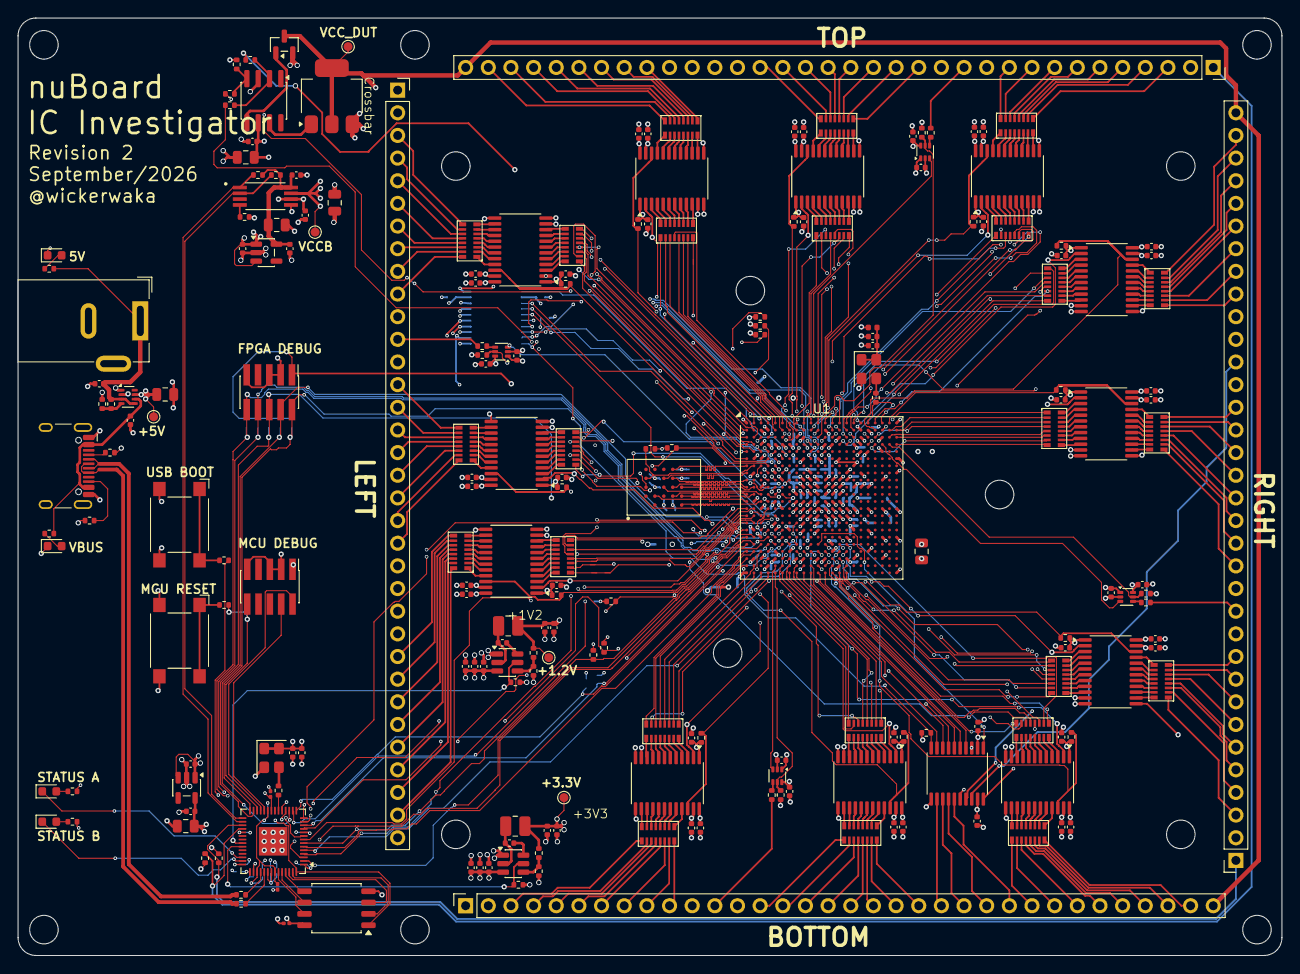
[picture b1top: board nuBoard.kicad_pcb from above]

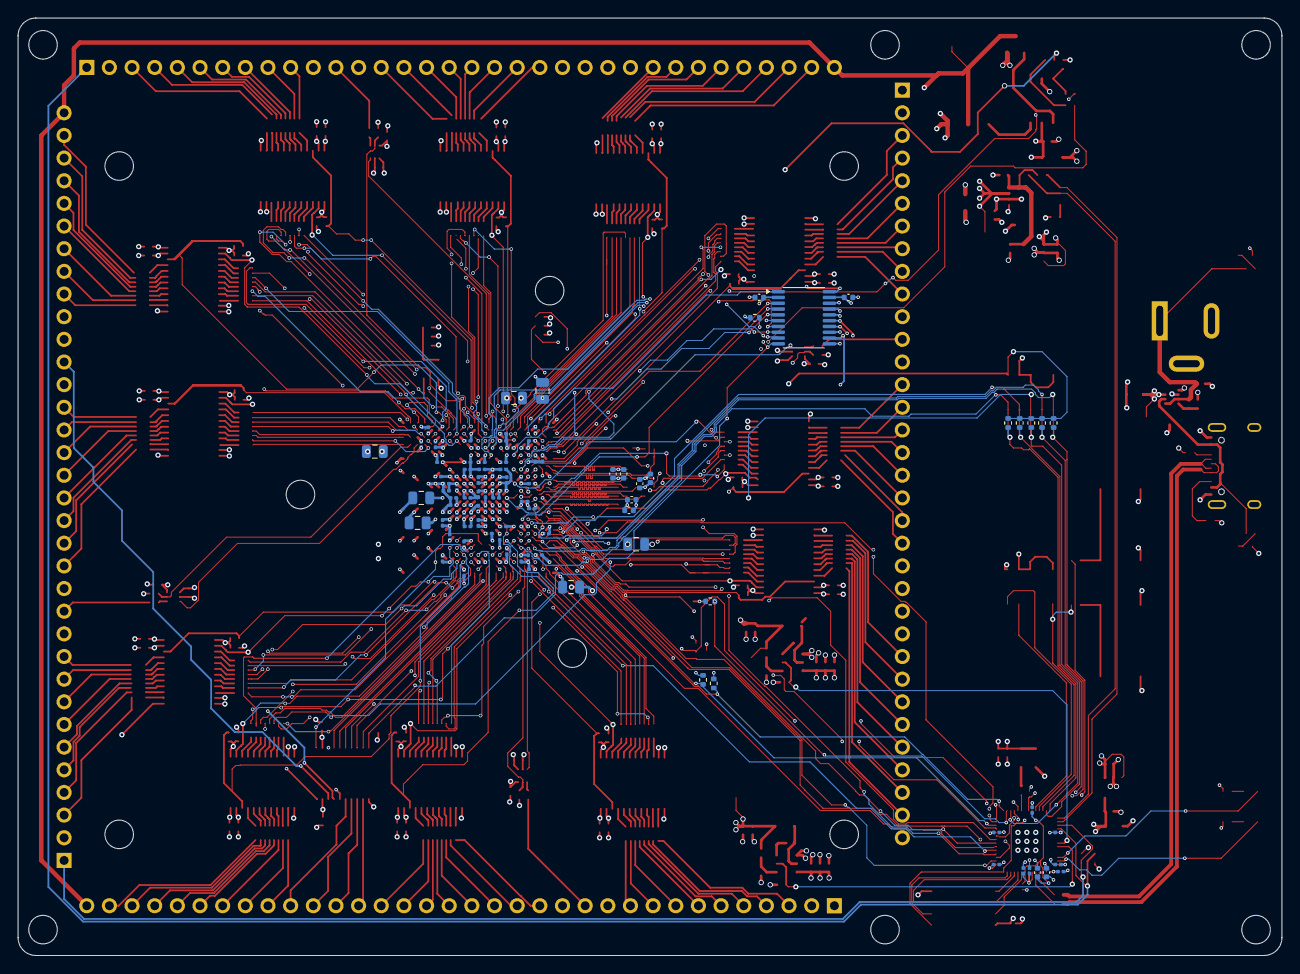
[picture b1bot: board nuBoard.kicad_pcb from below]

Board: 6 copper layers, 141.7 x 105.1 mm, 343 parts (114 on the bottom side), 549 nets.

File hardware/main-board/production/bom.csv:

Designator,Footprint,Quantity,Value,LCSC Part #
"C1, C131",0402,2,4.7u,C23733
"C10, C11, C118, C119, C12, C120, C121, C122, C123, C124, C125, C128, C129, C13, C130, C14, C15, C16, C17, C18, C19, C20, C21, C22, C23, C24, C25, C26, C27, C28, C29, C30, C31, C32, C33, C34, C35, C36, C37, C38, C39, C5, C6, C7, C8, C9",0201,46,0.1u 0201,C5142565
"C100, C114, C115, C86, C87, C90, C91, C93, C97",0805,9,10u,C15850
"C101, C104, C107, C110, C113, C116, C117, C132, C145, C146, C147, C148, C149, C150, C151, C152, C153, C154, C155, C156, C157, C158, C159, C160, C161, C162, C163, C164, C165, C166, C167, C168, C169, C170, C171, C172, C173, C174, C175, C176, C177, C178, C179, C180, C181, C182, C183, C184, C185, C186, C187, C188, C189, C190, C191, C192, C193, C194, C2, C3",0402,60,0.1u,C1525
"C102, C103, C108, C109",0402,4,22u,C22367823
"C105, C106, C111, C112",0402,4,10u,C315248
"C126, C127, C92, C94, C95, C96, C98, C99",0402,8,1u,C52923
"C133, C134, C4",0402,3,0.01u,C15195
"C40, C41, C42, C43, C44, C45, C46, C47, C48, C49, C50, C51, C52, C53, C54, C55, C56, C57, C58, C59, C60, C61, C62, C63, C64, C65, C66, C67, C68, C69, C70, C71, C72, C73, C74, C75, C76, C77, C78, C79, C80, C81, C82, C83",0201,44,0.01u 0201,C285010
"C84, C85, C88, C89",0805,4,1u,C28323
"D1, D2, D3, D4",0603,4,LED,C2286
FB1,0402,1,33ohm 100mhz,C160974
J1,PinHeader_2x05_P1.27mm_Vertical_SMD,1,FPGA Debug,C41376037
J2,BarrelJack_Wuerth_6941xx301002,1,Barrel_Jack_Switch,
J3,USB_C_Receptacle_HCTL_HC-TYPE-C-16P-01A,1,USB_C_Receptacle_USB2.0_16P,C2894897
J4,PinHeader_2x05_P1.27mm_Vertical_SMD,1,MCU Debug,C41376037
"J5, J6, J7, J8",PinSocket_1x34_P2.54mm_Vertical,4,Conn_01x34_Socket,
"L1, L2",0805,2,2.2uH,C16903
Q1,SOT-223-3_TabPin2,1,NVF5P03T3G,C895162
Q2,SOT-23,1,BSR802NL6327,C5240463
"R1, R10, R11, R13, R14, R15, R17, R18, R2, R24, R27, R28, R3, R31, R32, R33, R39, R4, R40, R5, R56, R57, R58, R59, R6, R60, R61, R62, R63, R64, R65, R66, R67, R68, R7, R70, R72, R74, R76, R77, R78, R79, R8, R9",0402,44,10K,C25744
"R12, R29, R30, R69, R71, R73, R75",0402,7,22,C25092
"R16, R19, R35, R38, R42, R43",0402,6,1K,C11702
"R20, R21",0402,2,5.1K,C25905
R22,0402,1,33.2K 1%,C122548
"R23, R26",0402,2,10K 1%,C25744
R25,0402,1,5.76K 1%,C11590
R34,0402,1,400,C2909358
"R36, R37, R41",0402,3,27,C25100
"RN1, RN10, RN11, RN12, RN13, RN14, RN15, RN16, RN17, RN18, RN19, RN2, RN20, RN21, RN22, RN23, RN24, RN3, RN4, RN5, RN6, RN7, RN8, RN9",YC248-JR-0722RL,24,22R,C695207
SW1,SW_SPST_Omron_B3FS-100xP,1,MCU_Reset,C271750
SW2,SW_SPST_Omron_B3FS-100xP,1,MCU_Boot,C271750
TP1,TestPoint_Pad_D1.0mm,1,+5V,
TP2,TestPoint_Pad_D1.0mm,1,+3.3V,
TP3,TestPoint_Pad_D1.0mm,1,+1.2V,
TP4,TestPoint_Pad_D1.0mm,1,VCC_DUT,
TP5,TestPoint_Pad_D1.0mm,1,VCCB,
U1,LFBGA-484_18x18mm_Layout22x22_P0.8mm,1,T120F484,C3277977
U10,SOIC-8_5.3x5.3mm_P1.27mm,1,W25Q128JVS,C97521
U11,QFN-56-1EP_7x7mm_P0.4mm_EP3.2x3.2mm,1,RP2040,C2040
U2,ISSI_TFBGA-24_6x8mm_P1.0mm,1,IS66WVH8M8BLL-100B1LI,C1349096
"U24, U25, U26, U27, U28, U29, U30, U31, U32, U33, U34, U35",TSSOP-24_4.4x7.8mm_P0.65mm,12,SN74LVC8T245PWR,C27643
U3,SOT-583-8,1,TPS2116DRL,C3235557
"U36, U41",TSSOP-20_4.4x6.5mm_P0.65mm,2,TXS0108EPW,C17206
"U37, U38, U39, U40",SOT-563,4,SN74LVC1T45DRL,C352970
"U4, U5",SOT-23-5,2,AP2112K-3.3,C23380830
"U6, U7",SOT-23-6,2,TPS563201,C116592
U8,SOIC-8_3.9x4.9mm_P1.27mm,1,UCC27524D,C465729
U9,SOP65P640X120-8N,1,TPS2111APWR,C471060
Y1,Oscillator_SMD_Abracon_ASE-4Pin_3.2x2.5mm,1,50Mhz,C717684
Y2,Oscillator_SMD_Abracon_ASE-4Pin_3.2x2.5mm,1,12Mhz,C596950
